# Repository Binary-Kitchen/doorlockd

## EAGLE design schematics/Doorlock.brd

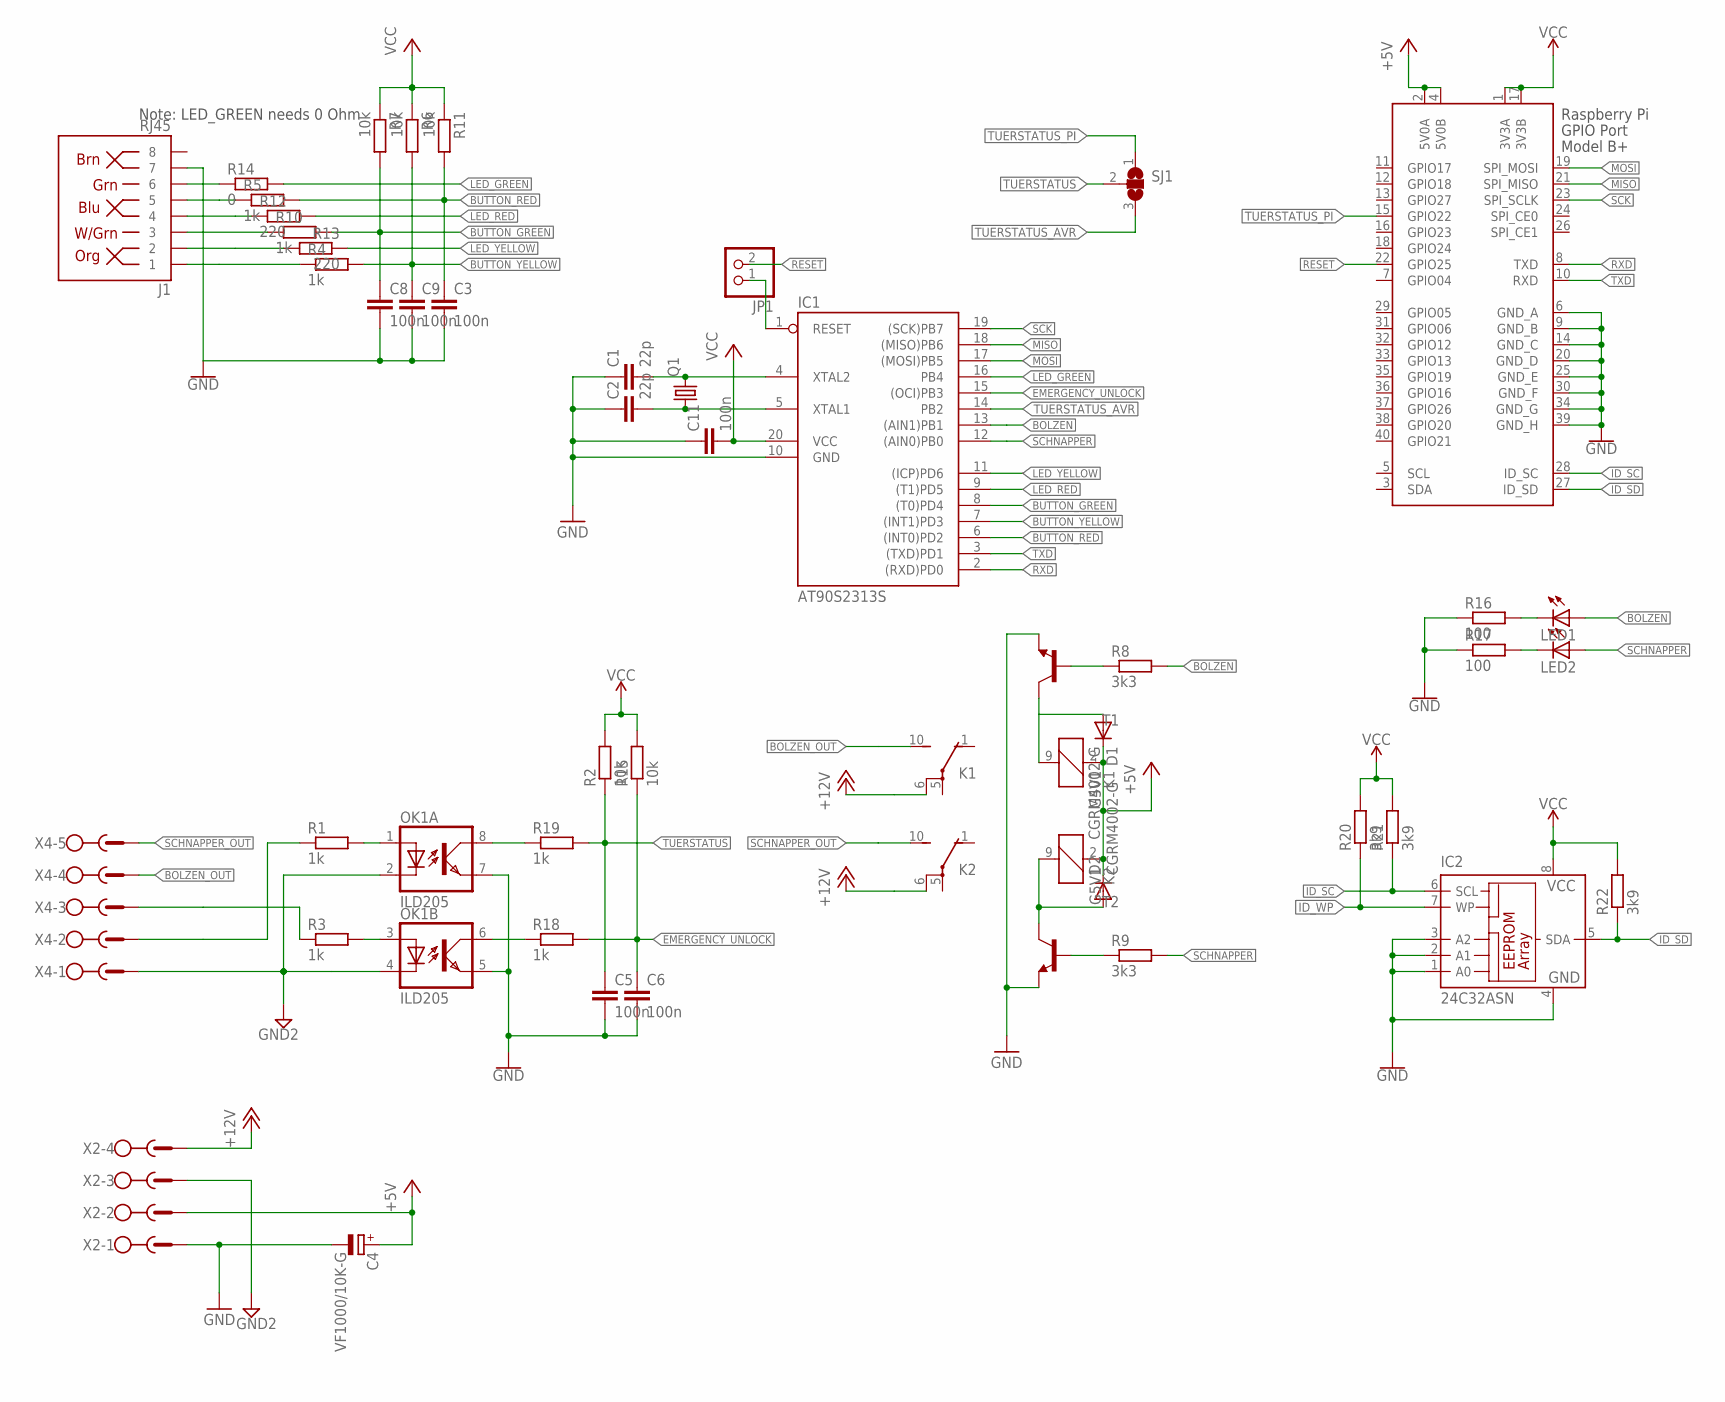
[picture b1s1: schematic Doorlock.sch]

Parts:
C1, C2: 22p; C0805
C3, C5, C6, C8, C9, C11: 100n; C0805
C4: VF1000/10K-G; UD-10X10_NICHICON
D1, D2: CGRM4002-G; SOD-123_MINI-SMA
IC1: AT90S2313S; SO20L
IC2: 24C32ASN; SO-08
J1: RJ45; RJ45-8
JP1: PINHD-1X2; 1X02
K1, K2: G5V1
LED1, LED2: LEDCHIP-LED0805; CHIP-LED0805
OK1: ILD205; SOIC08
Q1: CRYSTALHC49UP; HC49UP
R1, R3, R4, R5, R10, R18, R19: 1k; R0805
R2, R6, R7, R11, R15: 10k; R0805
R8, R9: 3k3; R0805
R12, R13: 220; R0805
R14: 0; R0805
R16, R17: 100; R0805
R20, R21, R22: 3k9; R0805
SJ1: SJ2W; SJ_2
T1, T2: BC817-16-NPN-SOT23-BEC; SOT23-BEC
X1: RASPI_BOARD_B+#_H; RASPI_BOARD_B+HAT
X2: RIA182-04
X4: RIA182-05

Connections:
+5V: C4.+, D1.C, D2.C, K1.2 (1), K2.2 (1), X1.2 (5V0A), X1.4 (5V0B), X2.2
+12V: K1.6, K2.6, X2.4
BOLZEN: IC1.13 ((AIN1)PB1), LED1.A, R8.2
BOLZEN_OUT: K1.10 (S), X4.4
BUTTON_GREEN: C8.1, IC1.8 ((T0)PD4), R7.2, R10.2
BUTTON_RED: C3.1, IC1.6 ((INT0)PD2), R5.2, R11.2
BUTTON_YELLOW: C9.1, IC1.7 ((INT1)PD3), R4.2, R6.2
EMERGENCY_UNLOCK: C6.1, IC1.15 ((OCI)PB3), R15.1, R18.2
GND: C1.1, C2.1, C3.2, C4.-, C5.2, C6.2, C8.2, C9.2, C11.1, IC1.10 (GND), IC2.1 (A0), IC2.2 (A1), IC2.3 (A2), IC2.4 (GND), J1.7, OK1.5 (EMIT), OK1.7 (EMIT), R16.1, R17.1, T1.E, T2.E, X1.6 (GND_A), X1.9 (GND_B), X1.14 (GND_C), X1.20 (GND_D), X1.25 (GND_E), X1.30 (GND_F), X1.34 (GND_G), X1.39 (GND_H), X2.1
GND2: OK1.2 (C), OK1.4 (C), X2.3, X4.1
ID_SC: IC2.6 (SCL), R21.1, X1.28 (ID_SC)
ID_SD: IC2.5 (SDA), R22.1, X1.27 (ID_SD)
ID_WP: IC2.7 (WP), R20.1
LED_GREEN: IC1.16 (PB4), R14.2
LED_RED: IC1.9 ((T1)PD5), R12.2
LED_YELLOW: IC1.11 ((ICP)PD6), R13.1
MISO: IC1.18 ((MISO)PB6), X1.21 (SPI_MISO)
MOSI: IC1.17 ((MOSI)PB5), X1.19 (SPI_MOSI)
unnamed: IC1.1 (RESET), JP1.1
unnamed: J1.6, R14.1
unnamed: OK1.6 (COL), R18.1
unnamed: OK1.3 (A), R3.2
unnamed: OK1.8 (COL), R19.1
unnamed: C1.2, IC1.4 (XTAL2), Q1.2
unnamed: C2.2, IC1.5 (XTAL1), Q1.1
unnamed: J1.3, R10.1
unnamed: J1.4, R12.1
unnamed: R1.1, X4.2
unnamed: J1.2, R13.2
unnamed: R3.1, X4.3
unnamed: OK1.1 (A), R1.2
unnamed: LED1.C, R16.2
unnamed: LED2.C, R17.2
unnamed: J1.1, R4.1
unnamed: J1.5, R5.1
unnamed: D2.A, K2.9 (2), T2.C
unnamed: D1.A, K1.9 (2), T1.C
unnamed: R8.1, T1.B
unnamed: R9.1, T2.B
RESET: JP1.2, X1.22 (GPIO25)
RXD: IC1.2 ((RXD)PD0), X1.8 (TXD)
SCHNAPPER: IC1.12 ((AIN0)PB0), LED2.A, R9.2
SCHNAPPER_OUT: K2.10 (S), X4.5
SCK: IC1.19 ((SCK)PB7), X1.23 (SPI_SCLK)
TUERSTATUS: C5.1, R2.1, R19.2, SJ1.2
TUERSTATUS_AVR: IC1.14 (PB2), SJ1.3
TUERSTATUS_PI: SJ1.1, X1.15 (GPIO22)
TXD: IC1.3 ((TXD)PD1), X1.10 (RXD)
VCC: C11.2, IC1.20 (VCC), IC2.8 (VCC), R2.2, R6.1, R7.1, R11.1, R15.2, R20.2, R21.2, R22.2, X1.1 (3V3A), X1.17 (3V3B)

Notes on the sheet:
Note: LED_GREEN needs 0 Ohm

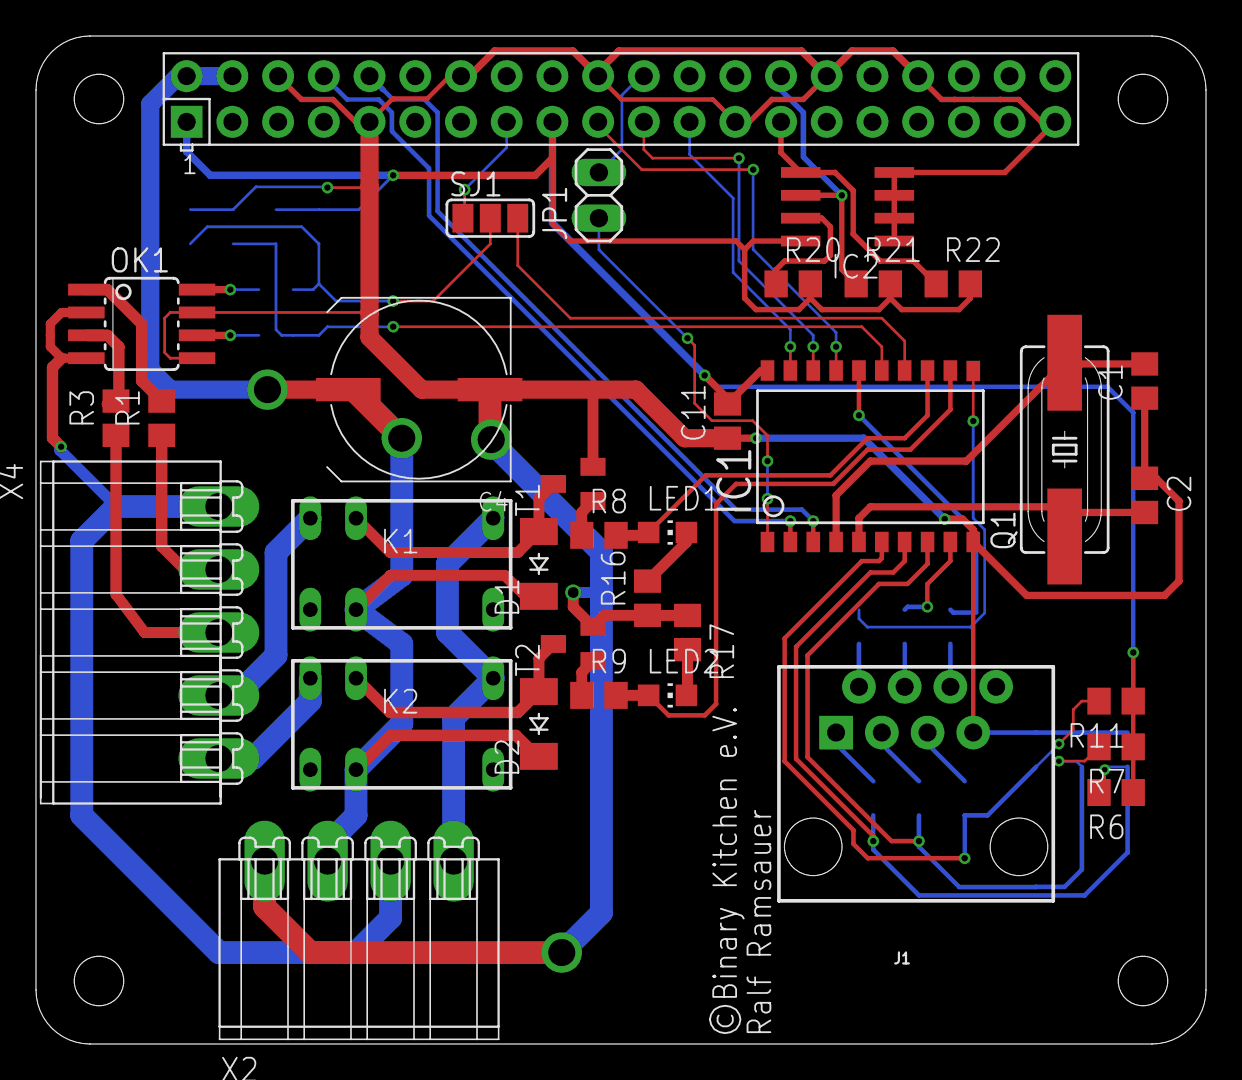
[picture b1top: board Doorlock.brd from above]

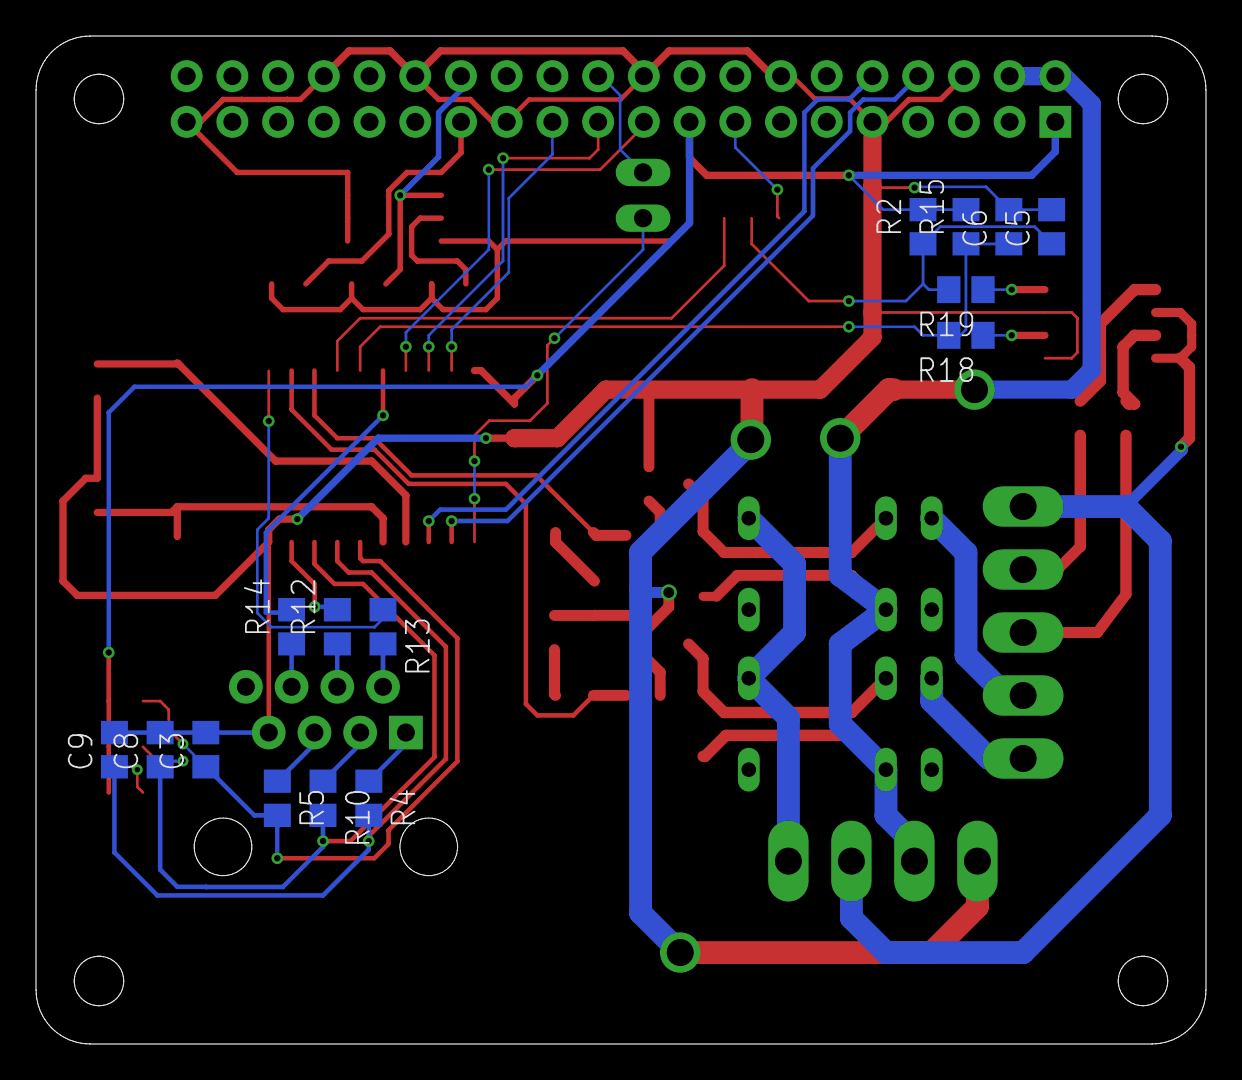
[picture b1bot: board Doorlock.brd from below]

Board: 2 copper layers, 65.0 x 56.0 mm, 49 parts (15 on the bottom side), 49 nets.

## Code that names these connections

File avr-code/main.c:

/*
 * doorlock-avr, AVR code of Binary Kitchen's doorlock
 *
 * Copyright (c) Binary Kitchen, 2018
 *
 * Authors:
 *  Ralf Ramsauer <ralf@binary-kitchen.de>
 *
 * This work is licensed under the terms of the GNU GPL, version 2.  See
 * the COPYING file in the top-level directory.
 */

#include "uart.h"

#include <ctype.h>
#include <stdbool.h>
#include <avr/io.h>
#include <avr/interrupt.h>
#include <util/delay.h>

#include "protocol.h"

#define RED	0x1
#define GREEN	0x2
#define YELLOW	0x4

#define SET_CONDITIONAL(predicate, port, pin) \
	if ((predicate)) \
		port |= (1 << pin); \
	else \
		port &= ~(1 << pin);

/* can either be red, green, or yellow */
static unsigned char state = RED;

enum state_source {
	BUTTON,
	COMM,
	TIMEOUT,
	EMERGENCY,
};

static inline void set_schnapper(bool state)
{
	SET_CONDITIONAL(state, PORTB, PB0);
}

static inline void set_bolzen(bool state)
{
	SET_CONDITIONAL(state, PORTB, PB1);
}

static inline void reset_timeout(void)
{
	TCNT1 = 0;
}

static void set_leds(void)
{
	static unsigned int counter = 0;
	bool pwm_cycle = ++counter % 20;

	if (pwm_cycle) {
		PORTD &= ~((1 << PD5) | (1 << PD6));
		PORTB &= ~(1 << PB4);
	}

	switch (state) {
	case RED:
		PORTD |= (1 << PD5);
		break;
	case YELLOW:
		PORTD |= (1 << PD6);
		break;
	case GREEN:
		PORTB |= (1 << PB4);
		break;
	}

	if (pwm_cycle)
		return;

	switch (state) {
	case RED:
		PORTD ^= (1 << PD6);
		PORTB ^= (1 << PB4);
		break;
	case YELLOW:
		PORTD ^= (1 << PD5);
		PORTB ^= (1 << PB4);
		break;
	case GREEN:
		PORTD ^= (1 << PD5);
		PORTD ^= (1 << PD6);
		break;
	}
}

static void update_state(unsigned char new_state, enum state_source source)
{
	char ret = 0;
	reset_timeout();

	if (new_state == state)
		return;
	state = new_state;

	switch (state) {
	case RED:
		set_bolzen(true);
		set_schnapper(false);
		ret = AVR_STATE_SWITCH_RED;
		break;
	case YELLOW:
		set_bolzen(false);
		set_schnapper(false);
		ret = AVR_STATE_SWITCH_YELLOW;
		break;
	case GREEN:
		set_bolzen(false);
		set_schnapper(true);
		ret = AVR_STATE_SWITCH_GREEN;
		break;
	}

	switch (source) {
	case BUTTON:
		uart_putc(toupper(ret));
		break;
	case EMERGENCY:
		uart_putc(AVR_EMERGENCY);
		break;
	case TIMEOUT:
		uart_putc(ret);
		break;
	case COMM:
	default:
		break;
	}
}

ISR(USART_RX_vect)
{
	unsigned char c = UDR;

	switch (c) {
	case AVR_STATE_SWITCH_RED:
		update_state(RED, COMM);
		break;
	case AVR_STATE_SWITCH_YELLOW:
		update_state(YELLOW, COMM);
		break;
	case AVR_STATE_SWITCH_GREEN:
		update_state(GREEN, COMM);
		break;
	}
}

ISR(TIMER1_OVF_vect)
{
	reset_timeout();
	update_state(RED, TIMEOUT);
}

static inline void timer_init(void)
{
	TIMSK |= (1 << TOIE1);
	TIFR |= (1 << TOV1);
	TCCR1A = 0;
	TCCR1B = (1 << CS12);
}

static inline void setup_ports(void)
{
	PORTB = 0;
	DDRB = (1 << PB4) | (1 << PB1) | (1 << PB0);

	PORTD = 0;
	DDRD = (1 << PD5) | (1 << PD6);
}

static inline bool is_emergency(void)
{
	return !(PINB & (1 << PB3));
}

static inline bool is_door_open(void)
{
	return !(PINB & (1 << PB2));
}

static unsigned char get_keys(void)
{
	unsigned char ret = 0;

	if (!(PIND & (1 << PD2))) ret |= RED;
	if (!(PIND & (1 << PD3))) ret |= YELLOW;
	if (!(PIND & (1 << PD4))) ret |= GREEN;

	return ret;
}

int main(void)
{
	unsigned char i;

	setup_ports();
	timer_init();
	uart_init();

	set_bolzen(true);
	reset_timeout();

	sei();

	for (;;) {
		if (is_emergency()) {
			update_state(GREEN, EMERGENCY);
		} else {
			i = get_keys();
			if (i & GREEN)
				update_state(GREEN, BUTTON);
			else if (i & YELLOW)
				update_state(YELLOW, BUTTON);
			else if (i & RED)
				update_state(RED, BUTTON);
		}
		set_leds();
	}
}

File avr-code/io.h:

#ifndef IO_H
#define IO_H

#include <stdbool.h>
#include <avr/io.h>

/*
 * Macros
 */
#define PIN(x) (*(&x - 2)) // Address Of Data Direction Register Of Port x 
#define DDR(x) (*(&x - 1)) // Address Of Input Register Of Port x

/*
 * Outputs
 */
#define PORT_BOLZEN    PORTB
#define PIN_BOLZEN     PB0

#define PORT_SCHNAPPER PORTB
#define PIN_SCHNAPPER  PB1

#define PORT_STATUS    PORTB
#define PIN_STATUS     PB2

/*
 * Inputs
 */
#define PORT_BUTTON_LOCK      PORTD
#define PIN_BUTTON_LOCK		  PD2

#define PORT_BUTTON_UNLOCK    PORTD
#define PIN_BUTTON_UNLOCK	  PD3

#define PORT_EMERGENCY_UNLOCK PORTD
#define PIN_EMERGENCY_UNLOCK  PD4

static inline bool is_emergency_unlock(void)
{
	return !(PIN(PORT_EMERGENCY_UNLOCK) & (1<<PIN_EMERGENCY_UNLOCK));
}

static inline bool is_button_unlock(void)
{
	return !(PIN(PORT_BUTTON_UNLOCK) & (1<<PIN_BUTTON_UNLOCK));
}

static inline bool is_button_lock(void)
{
	return !(PIN(PORT_BUTTON_LOCK) & (1<<PIN_BUTTON_LOCK));
}


static inline void schnapper_off(void)
{
	PORT_SCHNAPPER &= ~(1<<PIN_SCHNAPPER);
}

static inline void schnapper_on(void)
{
	PORT_SCHNAPPER |= (1<<PIN_SCHNAPPER);
}

static inline void bolzen_off(void)
{
	PORT_BOLZEN &= ~(1<<PIN_BOLZEN);
}

static inline void bolzen_on(void)
{
	PORT_BOLZEN |= (1<<PIN_BOLZEN);
}

static inline void status_off(void)
{
	PORT_STATUS &= ~(1<<PIN_STATUS);
}

static inline void status_on(void)
{
	PORT_STATUS |= (1<<PIN_STATUS);
}

static inline void io_init(void)
{
	// Set output directions
	DDR(PORT_SCHNAPPER) |= (1<<PIN_SCHNAPPER);
	schnapper_off();

	DDR(PORT_SCHNAPPER) |= (1<<PIN_BOLZEN);
	bolzen_off();

	DDR(PORT_STATUS) |= (1<<PIN_STATUS);
	status_off();

	// Set input directions and activate pull-ups
	DDR(PORT_BUTTON_UNLOCK) &= ~(1<<PIN_BUTTON_UNLOCK);
	PORT_BUTTON_UNLOCK |= (1<<PIN_BUTTON_UNLOCK);

	DDR(PORT_BUTTON_LOCK) &= ~(1<<PIN_BUTTON_LOCK);
	PORT_BUTTON_LOCK |= (1<<PIN_BUTTON_LOCK);
	
	DDR(PORT_EMERGENCY_UNLOCK) &= ~(1<<PIN_EMERGENCY_UNLOCK);
	PORT_EMERGENCY_UNLOCK |= (1<<PIN_EMERGENCY_UNLOCK);
}

#endif

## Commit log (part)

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2015-09-24 added rest of the software
2015-09-24 Fixed small bug
2015-09-24 Added comments
2015-09-24 Switched button type from open to close
2015-09-24 Inversed logic of Doorlight
2015-09-24 removed wiringPi
2015-09-24 Removed Door State from Logic
2015-09-24 Rewrite of Door class
    Removed old epaper display and added stub for qrcode printing.
2015-09-24 Added Lock Button
2015-09-24 Added proper json-cpp include directory
2015-09-24 New LDAP default URI
2015-09-24 Added mutex to door.cpp to prevent lock collissions
2015-09-24 Added schematics of controller board
2015-09-24 Added Pre/Post Lock/Unlock Scripts
2015-09-24 Added new AVR software
2015-09-24 Removed manual change of tokenTimeout
    Epaper display is gone, this is not necessary any more.
2015-09-24 Activated the 'status' functionality
2015-09-24 Moved Command handling from logic to main
2015-09-24 Code style
2015-09-24 Outsourced timer and external interupt initialization
2015-09-24 Removed foreground option (default now)
2015-09-24 Implemented better Response handling
2015-09-24 doorlockd now uses doorcmds.h
2015-09-24 Moved JSON parsing to main.cpp
2015-09-24 Added proper Response handling
2015-09-24 Refactored action to command
2015-09-24 added more documentation
2015-09-24 moved License file
2015-09-24 Improved error handling
2015-09-24 Changed default serial port
2015-09-24 Bugfix
    socket might be closed after session-thread is spawned.
    socket might throw errors very early.
2015-09-24 Renamed main.cpp to doorlockd.cpp
2015-09-24 Small fix
2015-09-24 Added proper client and doormessage classes
2015-09-24 Bugfix: Timeout was uninitialized
2015-09-24 Added door callbacks
2015-09-24 Removed unneeded function
2015-09-24 Added Client messages
2015-09-24 Added version information
2015-09-24 Typos
2015-09-24 Resend version string after redirection stdout
2015-09-24 added install rule for doorlock-client
2015-09-25 Write first tokenupdate on session initialization
2015-09-25 Moved common code parts to static library
2015-09-28 Created new MainWindow QT Frontend
2015-09-29 Added mainwindow.h to CMakeLists.txt
2015-09-29 Bugfix: QR code generation was case insensitive
    Also changed Qstring back to std::string
2015-09-29 Improved directory structure
2015-09-29 Bugfix
2015-09-30 Switched to asynchronous asio handling
2015-09-30 Changed window sizes
2015-10-01 Big rewrite of several things
    - Data type Token changed from uint64_t to std::string
    - Added new class "Request" that describes a JSON TCP request
    - Classes may now throw Responses for proper error handling
    - Removed JSON parsing from Logic
    - proper Error handling everywhere
    - Many small fixes
2015-10-01 Automatic reconnect
2015-10-01 automatic shutdown & reconnection
2015-10-02 common code style
2015-10-02 removed usings from logger.cpp
2015-10-02 Better layout for LCD
2015-10-05 Added new LED images and removed old templante.png
2015-10-05 Bugfix & logical change
    - Improved doormessage
    - Moved isOpen from Doormessage to Logic
2015-10-07 Added new define for share-location
2015-10-07 Added doorlock sounds
2015-10-07 Defaulted location of LED pictures
2015-10-11 Added new wave class to CMakeLists.txt
2015-10-11 Cached playback of audio files
    doorlock_client now caches wave files in memory for faster playback.
    LibAO is used for audio playback and libsndfile for wave file header
    parsing.
2015-10-27 Fix JSON Bug
    Json::Values do not necessarily need to be JSON objects. This Patch
    checks if the JSON::Value is in deed an object.
    Reported-by: Markus Dollinger <dolli@ignifax.de>
2016-04-03 Logic: Allow tokens of arbitrary length
    Make token size dynamically adjustable. Shorter tokens are absolutely
    sufficient and simplify the manual copying of tokens
2016-04-11 Adjust DEFAULT_BINDDN to new LDAP scheme
2016-04-11 - Added default Cmake and CLion/intellij directories to .gitignore - Small refactoring in CMakeLists.txt. Possible bug fix with include_directories(${Boost_INCLUDE_DIRS}) (was located before find_pac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
2016-04-23 Fix boost include bug
2016-04-23 Add debugging output to CMakeLists.txt
2016-04-24 Use aplay command for playing sounds
    This basically reverts 5c8ca78c99dae2a193284a03693ea4968b59f475.
    Using libao + sndfile was a bad idea...
2016-04-24 [TASK] Replace status LED with Binary-Kitchen logo
2016-07-17 Cmake: Gcc: do not warn on unused results
2016-07-17 UI: refactor tokenLabel to address_label
2016-07-17 clientmessage: add token regex and getter
2016-07-18 scripts: Wake up cashdesk PC
2016-07-20 Doorlockd: Replace logfile by logdir
    In future, we might have several different logfiles.
2016-07-20 Door: Refactor system() to own function
    Preparatory work for script logging
2016-07-20 Door: Redirect output to logfile
    And use nohup for detached call.
2016-07-21 doorlock-client: Add more error output
2016-07-21 doorlock-client: be even more verbose
2016-07-31 Fix QT quirk
    So far, we used QT interfaces in a wrong way. QT is not thread safe, so
    use its signal/slot concept and move network communication stuff to a
    separate QThread.
2017-01-06 scripts: replace mac
    we have a new cash-desk PC
2018-03-18 Reimplement doorlockd in python
2018-03-18 Clean up imports
2018-03-18 socketio: deliver local static copy of scripts
2018-03-18 doorlockd.py: remove argparse dependency
    by replacing its logic with flask's config parameter file.
2018-03-18 config: serve local bootstrap and jquery copies
2018-03-18 index: refactor render_field to render_field_label
2018-03-18 doorlockd.py: move emit status to Logic class
2018-03-18 display: reindent
2018-03-18 Add TODOs
2018-03-18 doorlockd: add simulation mode
2018-03-18 doorlockd.py: Add lock/unlock scripts
2018-03-19 doorlockd.py: Add RS232 logic
2018-03-19 doorlockd.py: Add schnapper support
2018-03-20 doorlockd.py: remove Markup import statement
2018-03-20 doorlockd.py: Add compatibility layer for old doorlockd-app
    This commit will be reverted once everyone has updated their app.
2018-03-22 Add more TODOs
2018-03-22 config: don't run hooks
    For the moment, don't run hooks
2018-03-22 Remove TODO entry
2018-03-23 doorlockd: display: add autorefresh interval
    10 minutes sounds reasonable
2018-03-23 remove old code
2018-03-23 doorlockd.py: improve front end conversion
2018-04-03 changed socketio async mode from None to 'threading' in order to function correctly with python threads
2018-05-21 Send lock/unlock messages using retain flag
2018-05-21 Added Apple specific meta tag
    This meta tag leads to a real full screen app.
    See https://developer.apple.com/library/content/documentation/AppleApplications/Reference/SafariHTMLRef/Articles/MetaTags.html
2018-08-23 doorlockd: Implement doorlock API
    This will be used in the future Android App.
    /api only allows POST requests. POST variables:
    - user
    - pass
    - command
    Supported commands: "status", "lock", "unlock"
2018-08-28 Remove deprecated API
    We have a new app -- let's remove this.
2018-09-02 Split up simulation of LDAP and serial
2018-09-03 Prepare doorlock for new states
2018-09-03 Add the current state to the response
2018-09-03 Rework AlreadyLocked and AlreadyUnlocked
    Better use the AlreadyActive semantics, which signalises that a state,
    no matter which state in particular, is already active.
2018-09-03 Factor out string to DoorState conversion, and support present command
2018-09-03 avr: remove superfluous function
2018-09-03 avr: improve logic
2018-09-03 avr: support emergency unlock
2018-09-03 Design a button case
2018-09-05 Add proper debugging mode
    For production, only listen on localhost, in Debug mode,
    allow anything from 0.0.0.0
2018-09-05 move sound specification from config to source
2018-09-05 Flask: specify correct root_path
    We need that for package installation.
2018-09-07 avr: choose our own programmer
2018-09-07 doorlockd: Flask: disable use_reloader
    This spawns the process twice which duplicates the UART thread, which,
    of course, leads to silly races.
2018-09-07 doorlockd: hooks: simplify hooks
    and add present state
2018-09-07 doorlockd: fix logic bug
    We don't want to continue if we actually want to close.
2018-09-08 Add Makefile
2018-09-08 schematics: Update Resistor values
2018-09-08 schematics: decouple optocoupler
2018-09-08 schematics: board: move RJ45 jack to the left
2018-09-08 doorlockd: templates: fix bug in meta tags
2018-09-09 schematics: add Raspberry Pi Hat EEPROM
2018-09-09 PKGBUILD: add python-ldap dependency
2018-09-09 schematics: Add BOM and Reichelt link
2018-09-09 doorlockd: templated: improve layout
2018-09-17 Parameterise more settings
2018-09-17 Makefile: install doorlockd-passwd
2018-09-17 doorlockd: amend default config path for local credential storage
2018-10-06 avr: Add fuse rule to Makefile
2018-10-06 avr: reverse bolzen logic
    And set initial state
2018-10-06 Add TODO list
2018-10-06 scripts: update mqtt topics
2018-10-07 PKGBUILD: add more dependencies
2018-10-07 doorlockd: remove superfluous code
    No more users, drop it.
2018-10-16 pydoorlock: extract DoorState
2018-10-16 pydoorlock: switch to new config parser
    We want to use doorlockd for more than just serving webapps. Get rid of the
    Flask config parser and use python's own config parser.
2018-10-16 pydoorlock: Condense locality of Flask stuff
2018-10-16 doorlockd: propagate cfg through Logic
2018-10-16 doorlockd: move sounds to DoorHandler
2018-10-16 doorlockd: move all scripting stuff to DoorHandler
    Use this chance to get rid of most global variables.
2018-10-16 pydoorlock: Doorlock: remove redundant parentheses
2018-10-16 pydoorlock: minor stylistic fixups
2018-10-16 pydoorlock: Align API requests to latest changes
2018-10-16 fix doorlockd config
2018-10-16 doorlockd.default.cfg: fall back to default settings
2018-10-16 PKGBUILD: add python-pip as dependency
2018-10-18 configs: fix RUN_HOOKS
2018-12-08 Authenticator: automatically choose authentication backend
    and test other backends, if one fails.
    Written-by: Rudolf Mayerhofer <rm@eightyfive.net>
    [ralf: also remove the authentication method from any other code path]
2019-02-22 doorlockd.cfg: move comment
    It's at the wrong place...
2019-02-22 doorlockd: update copyright
2019-06-13 improve authentication log messages
2019-06-14 Makefile: Add a proper package rule
2019-06-14 Makefile: Add a proper clean rule
2019-06-14 pydoorlock: use definitions in Protocol.py
    We now share definitions. Use them.
2019-06-14 pydoorlock: Config: Only use one config file
2019-06-15 Introduce etc directory
2019-06-15 doorstate: Use variable instead of constant value
2019-06-18 PKGBUILD: add missing dependency pyserial
2019-06-23 doorstate: reimplement doorstate in python
    Furthermore, add initial support for the alarm topic.
2019-06-23 VERSION: open 2.1 development cycle
    Better late than never: open the 2.1 development cycle
2019-07-07 doorstate: automatically reconnect if mqtt broker fails
    We had a bug: doorstate didn't reconnect to the broker if it temporarily
    disappeared.
    Fix this by using start_loop() (which starts a thread that observes the
    broker and automatically reconnects) instead of the synchronous loop()
    method.
    Thomas Basler <github.thomas@familie-basler.net>
2019-07-08 ansible: add missing newline
2019-07-08 gitignore: add ci/out
    Our artefacts go there -- ignore them
2019-07-08 ci: Makefile: Automount /boot
2019-07-08 add ansible roles for automatic deployment to any arch linux system
2019-07-08 ansible: install some usefull tools
2019-10-27 it's not a door, it's a tardis
    Time And Relative Dimension(s) In Space
2020-06-06 doorstate: publish state on startup
2020-10-08 Add http sent event client
2020-10-08 Remove socket.io dependency and use http server sent events instead
2020-10-08 doorlockd-slave: implement push notification thread
2021-11-22 Config: reformat whitespace according to PEP8
2021-11-22 Authenticator: reformat whitespace accoring to PEP8
2021-11-22 WebApp: remove duplicate function definition
2021-11-22 Makefile: don't force reintall of dependencies
2021-11-22 TESTING
2021-11-22 trallala
2021-11-22 Makefile: use setup.py instead of pip
    Abandons the strange 'dependency_links.txt'-bug.
2022-11-16 Refactor pydoorlock to support multiple backends
2022-11-17 Sort Imports
    Sort imports for AvrDoorlock.py, DoorlockBackend.py, NukiBridge.py,
    SimulationBackend.py
2022-11-17 etc/doorlock.cfg: Remove unused keys and fix format
2022-11-17 Doorlock Backends: Add license header
2022-11-17 new python dependency: requests
    We depend on requests for handling the http requests for the nuki
    backend.
2023-11-04 Doorlock.py: make eperm_insults a list
    choose_insult fails with a dict, so make it a list.

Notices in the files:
schematics/Doorlock.brd:
©Binary Kitchen e.V.
parts and their libraries:
SparkFun-Connectors: Licensing: Creative Commons ShareAlike 4.0 International - https://creativecommons.org/licenses/by-sa/4.0
